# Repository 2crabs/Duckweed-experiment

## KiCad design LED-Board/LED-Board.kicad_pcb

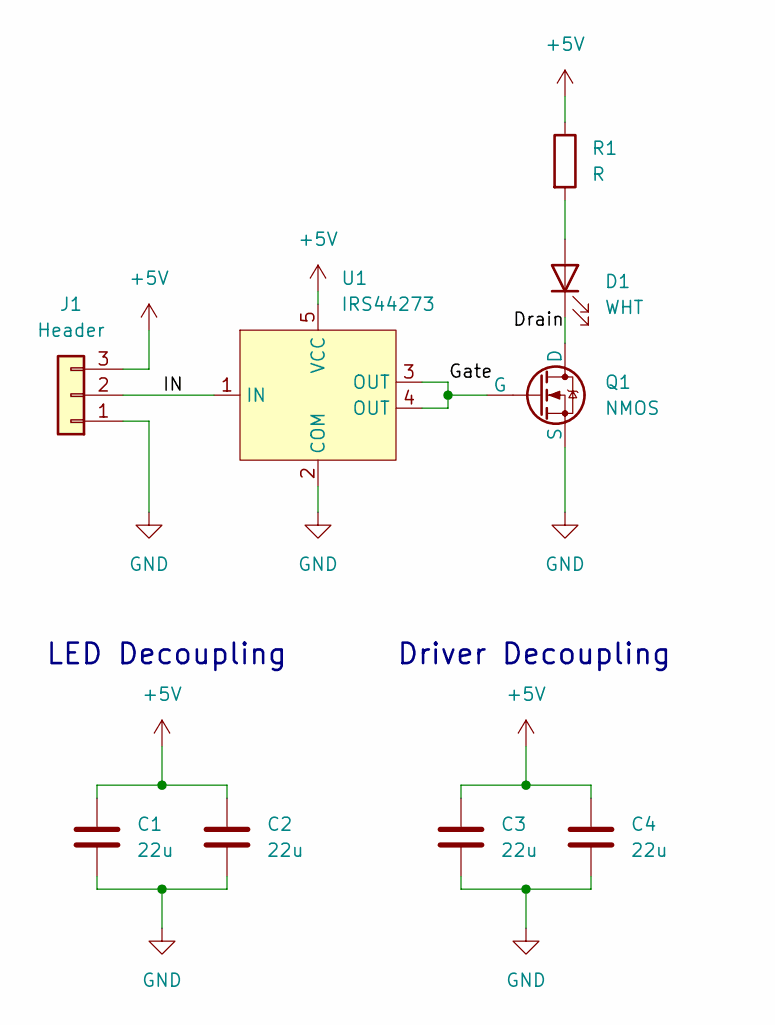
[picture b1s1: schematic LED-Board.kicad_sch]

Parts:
C1, C2, C3, C4: 22u; C_0805_2012Metric_Pad1.18x1.45mm_HandSolder
D1: WHT; JB3030
J1: Header; PinHeader_1x03_P2.54mm_Vertical
Q1: NMOS; SOT-23
R1: R; R_2010_5025Metric_Pad1.40x2.65mm_HandSolder
U1: IRS44273; SOT-23-5_HandSoldering

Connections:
+5V: C1.1, C2.1, C3.1, C4.1, J1.3, R1.1, U1.5 (VCC)
/Drain: D1.1 (K), Q1.3 (D)
/Gate: Q1.1 (G), U1.3 (OUT), U1.4 (OUT)
/IN: J1.2, U1.1 (IN)
GND: C1.2, C2.2, C3.2, C4.2, J1.1, Q1.2 (S), U1.2 (COM)
unnamed: D1.2 (A), R1.2

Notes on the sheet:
Driver Decoupling
LED Decoupling

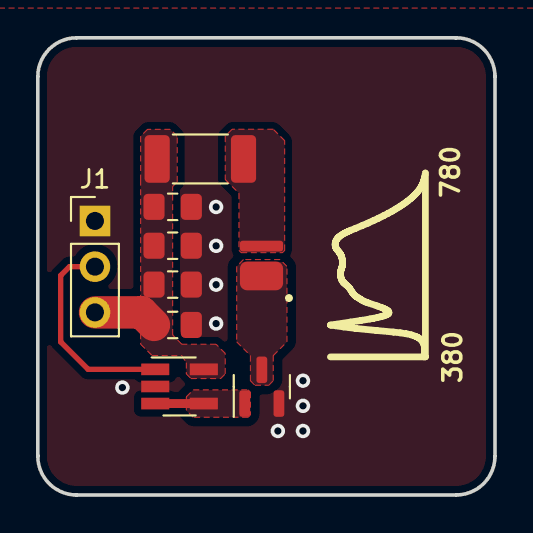
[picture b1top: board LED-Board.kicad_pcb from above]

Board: 2 copper layers, 25.4 x 25.4 mm, 9 parts (0 on the bottom side), 6 nets.

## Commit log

2025-12-26 Created project structure
2025-12-30 Added schematic symbols
2025-12-30 Added basic Typst setup
2025-12-30 Added test data
2026-01-08 Ignore .idea/
2026-01-08 Started basic python script
2026-01-08 Updated Typst doc
2026-01-13 Working masks
2026-01-13 Continued Background
2026-01-14 Continued
2026-01-27 Procedure draft
2026-02-09 Updated PCB
2026-02-09 Updated Formatting
2026-02-18 Measurements
2026-03-02 Added all data
2026-03-12 Appendix
2026-03-14 Conclusion
2026-03-14 Photos and threshold
2026-03-14 Final
